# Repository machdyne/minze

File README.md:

# Minze Computer

Minze is an FPGA computer designed by Lone Dynamics Corporation.

This repo contains schematics, PCB layouts, pinouts, a 3D-printable case, example gateware and documentation.

Find more information on the [Minze product page](https://machdyne.com/product/minze-computer/).

## Programming Minze

Minze has a JTAG interface and ships with a [DFU bootloader](https://github.com/machdyne/tinydfu-bootloader) that allows the included flash [MMOD](https://machdyne.com/product/mmod) to be programmed over the USB-C port.

### DFU

The DFU bootloader is available for 5 seconds after power-on, issuing a DFU command during this period will stop the boot process until the DFU device is detached. If no command is received the boot process will continue and the user gateware will be loaded.

Install [dfu-util](http://dfu-util.sourceforge.net) (Debian/Ubuntu):

```
$ sudo apt install dfu-util
```

Update the user gateware on the flash MMOD:

```
$ sudo dfu-util -a 0 -D image.bit
```

Detach the DFU device and continue the boot process:

```
$ sudo dfu-util -a 0 -e
```

It is possible to update the bootloader itself using DFU but you shouldn't attempt this unless you have a JTAG programmer (or another method to program the MMOD) available, in case you need to restore the bootloader.

### JTAG

These examples assume you're using a "USB Blaster" JTAG cable, see the header pinout below. You will need to have [openFPGALoader](https://github.com/trabucayre/openFPGALoader) installed.

Program the configuration SRAM:

```
openFPGALoader -c usb-blaster image.bit
```

Program the flash MMOD:

```
openFPGALoader -f -c usb-blaster images/bootloader/tinydfu_minze.bit
```

## Blinky 

Building the blinky example requires [Yosys](https://github.com/YosysHQ/yosys), [nextpnr-ecp5](https://github.com/YosysHQ/nextpnr) and [Project Trellis](https://github.com/YosysHQ/prjtrellis).

Assuming they are installed, you can simply type `make` to build the gateware, which will be written to output/blinky.bin. You can then use [openFPGALoader](https://github.com/trabucayre/openFPGALoader) or dfu-util to write the gateware to the device.

## Linux

See the [Kakao Linux](https://github.com/machdyne/kakao) repo for the latest instructions.

### Prebuilt Images

Prebuilt gateware capable of running Linux is available in the `images/v1` directory.

These images support a serial console on the PMOD socket. You can use a standard USB-UART PMOD to access the BIOS, boot messages and serial console.

### Building Linux-capable Gateware

Please follow the setup instructions in the [linux-on-litex-vexriscv](https://github.com/litex-hub/linux-on-litex-vexriscv) repo and then:

1. Build the Linux-capable gateware:

```
$ cd linux-on-litex-vexriscv
$ ./make.py --board=minze --dcache-size=64 --icache-size=64 --uart-baudrate=115200 --build
$ ls build/minze
```

2. Write the gateware to the MMOD using USB DFU:

```
$ sudo dfu-util -a 0 -D build/minze/gateware/minze.bit
```

3. Copy the device tree binary `build/minze/minze.dtb` to a FAT-formatted MicroSD card.

## JTAG Header

The 3.3V JTAG header can be used to program the FPGA SRAM as well as the MMOD flash memory. It can also be used to provide power (5V) to the board.

```
6 5
4 3
2 1
```

| Pin | Signal |
| --- | ------ |
| 1 | TCK |
| 2 | TDI |
| 3 | TDO |
| 4 | TMS |
| 5 | 5V0 |
| 6 | GND |

## Board Revisions

| Revision | Notes |
| -------- | ----- |
| V1 | Initial production version |

## License

The contents of this repo are released under the [Lone Dynamics Open License](LICENSE.md) with the following exceptions:

- The KiCad design files contain parts of the [kicad-pmod](https://github.com/mithro/kicad-pmod) library which is released under the [Apache License, Version 2.0](https://www.apache.org/licenses/LICENSE-2.0.html).

- The KiCad design files may contain symbols and footprints released under other licenses; please contact us if we've failed to give proper attribution.

Note: You can use these designs for commercial purposes but we ask that instead of producing exact clones, that you either replace our trademarks and logos with your own or add your own next to ours.

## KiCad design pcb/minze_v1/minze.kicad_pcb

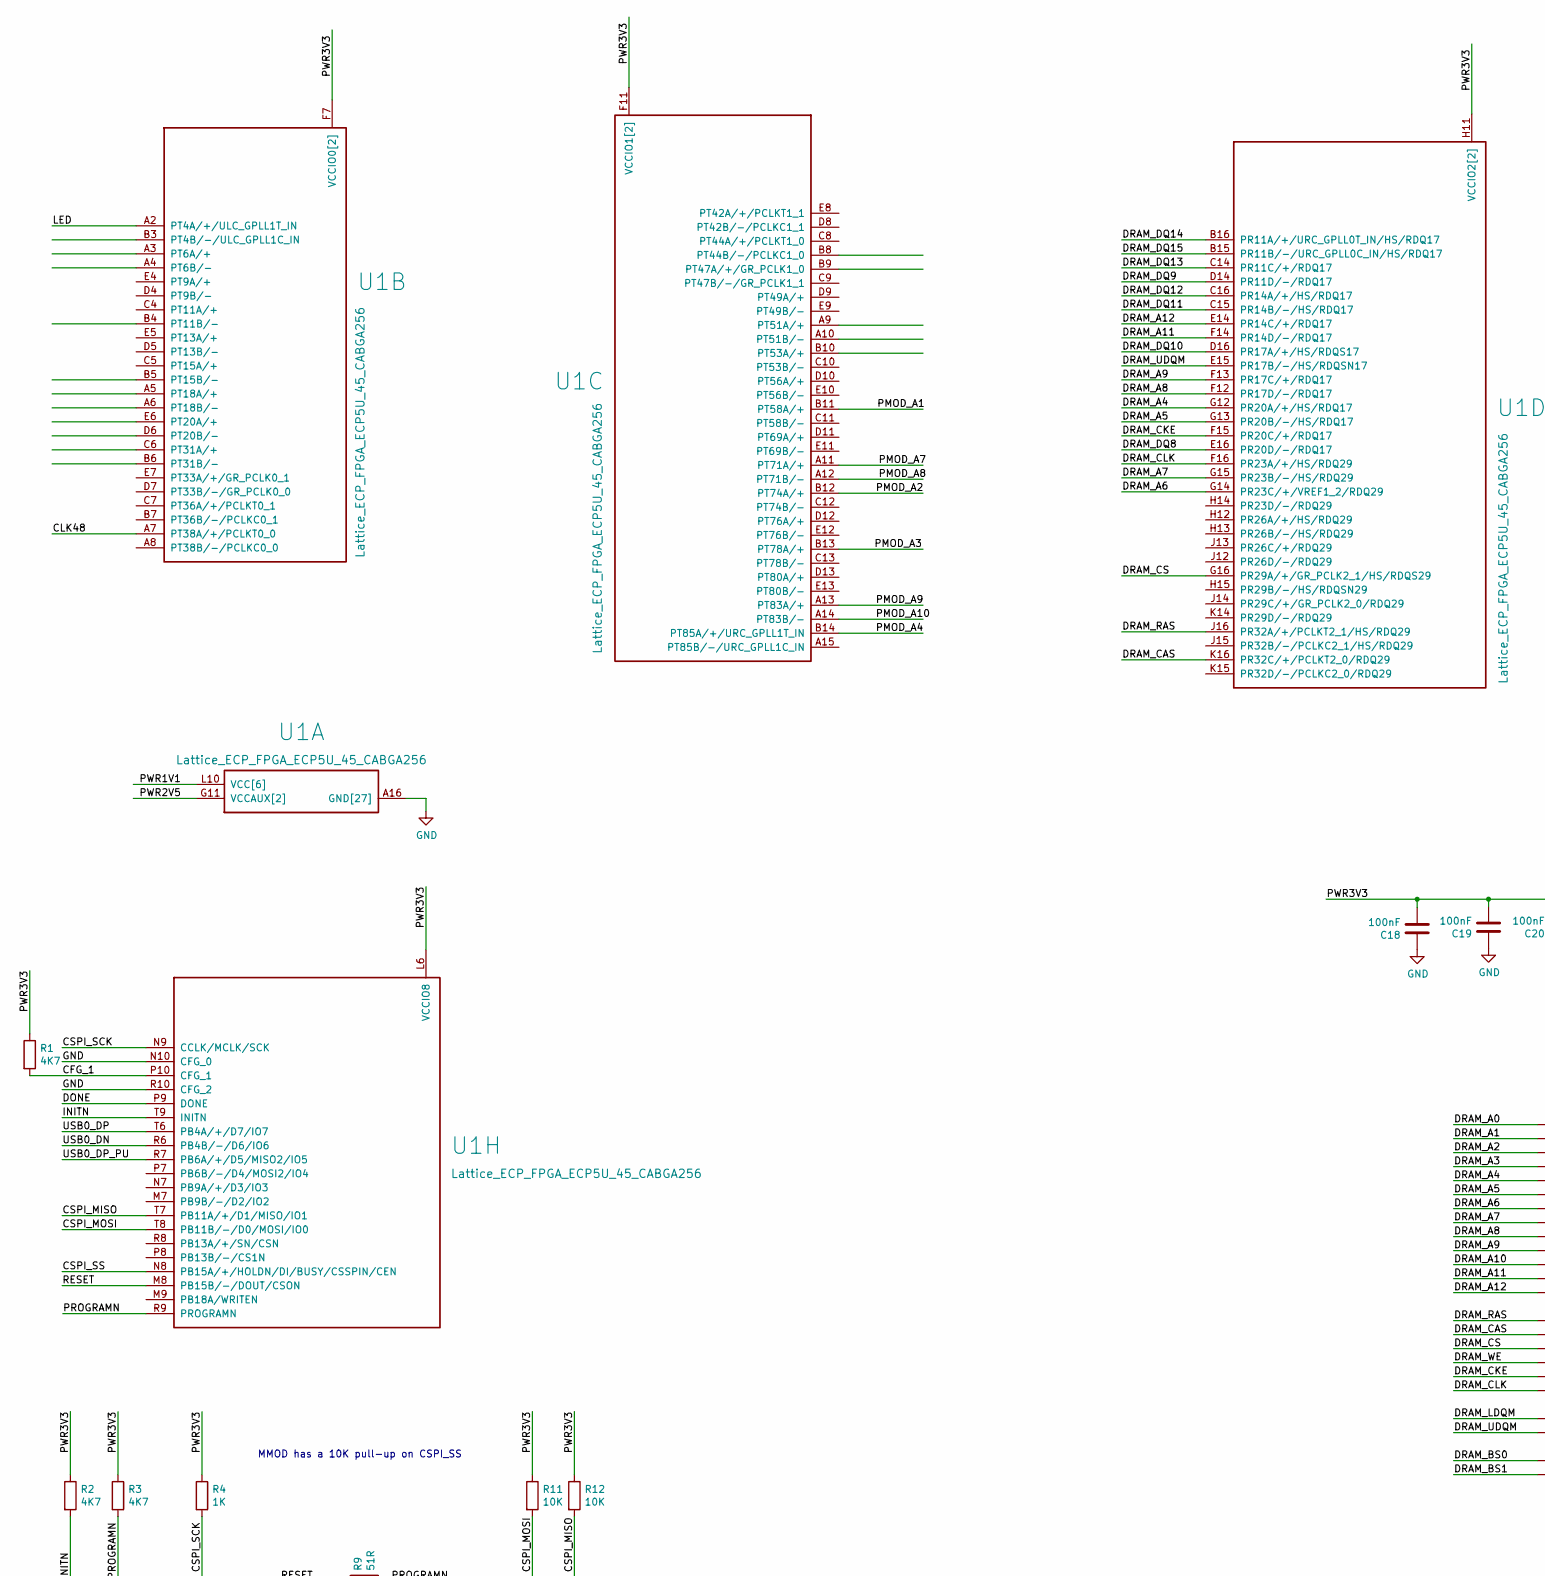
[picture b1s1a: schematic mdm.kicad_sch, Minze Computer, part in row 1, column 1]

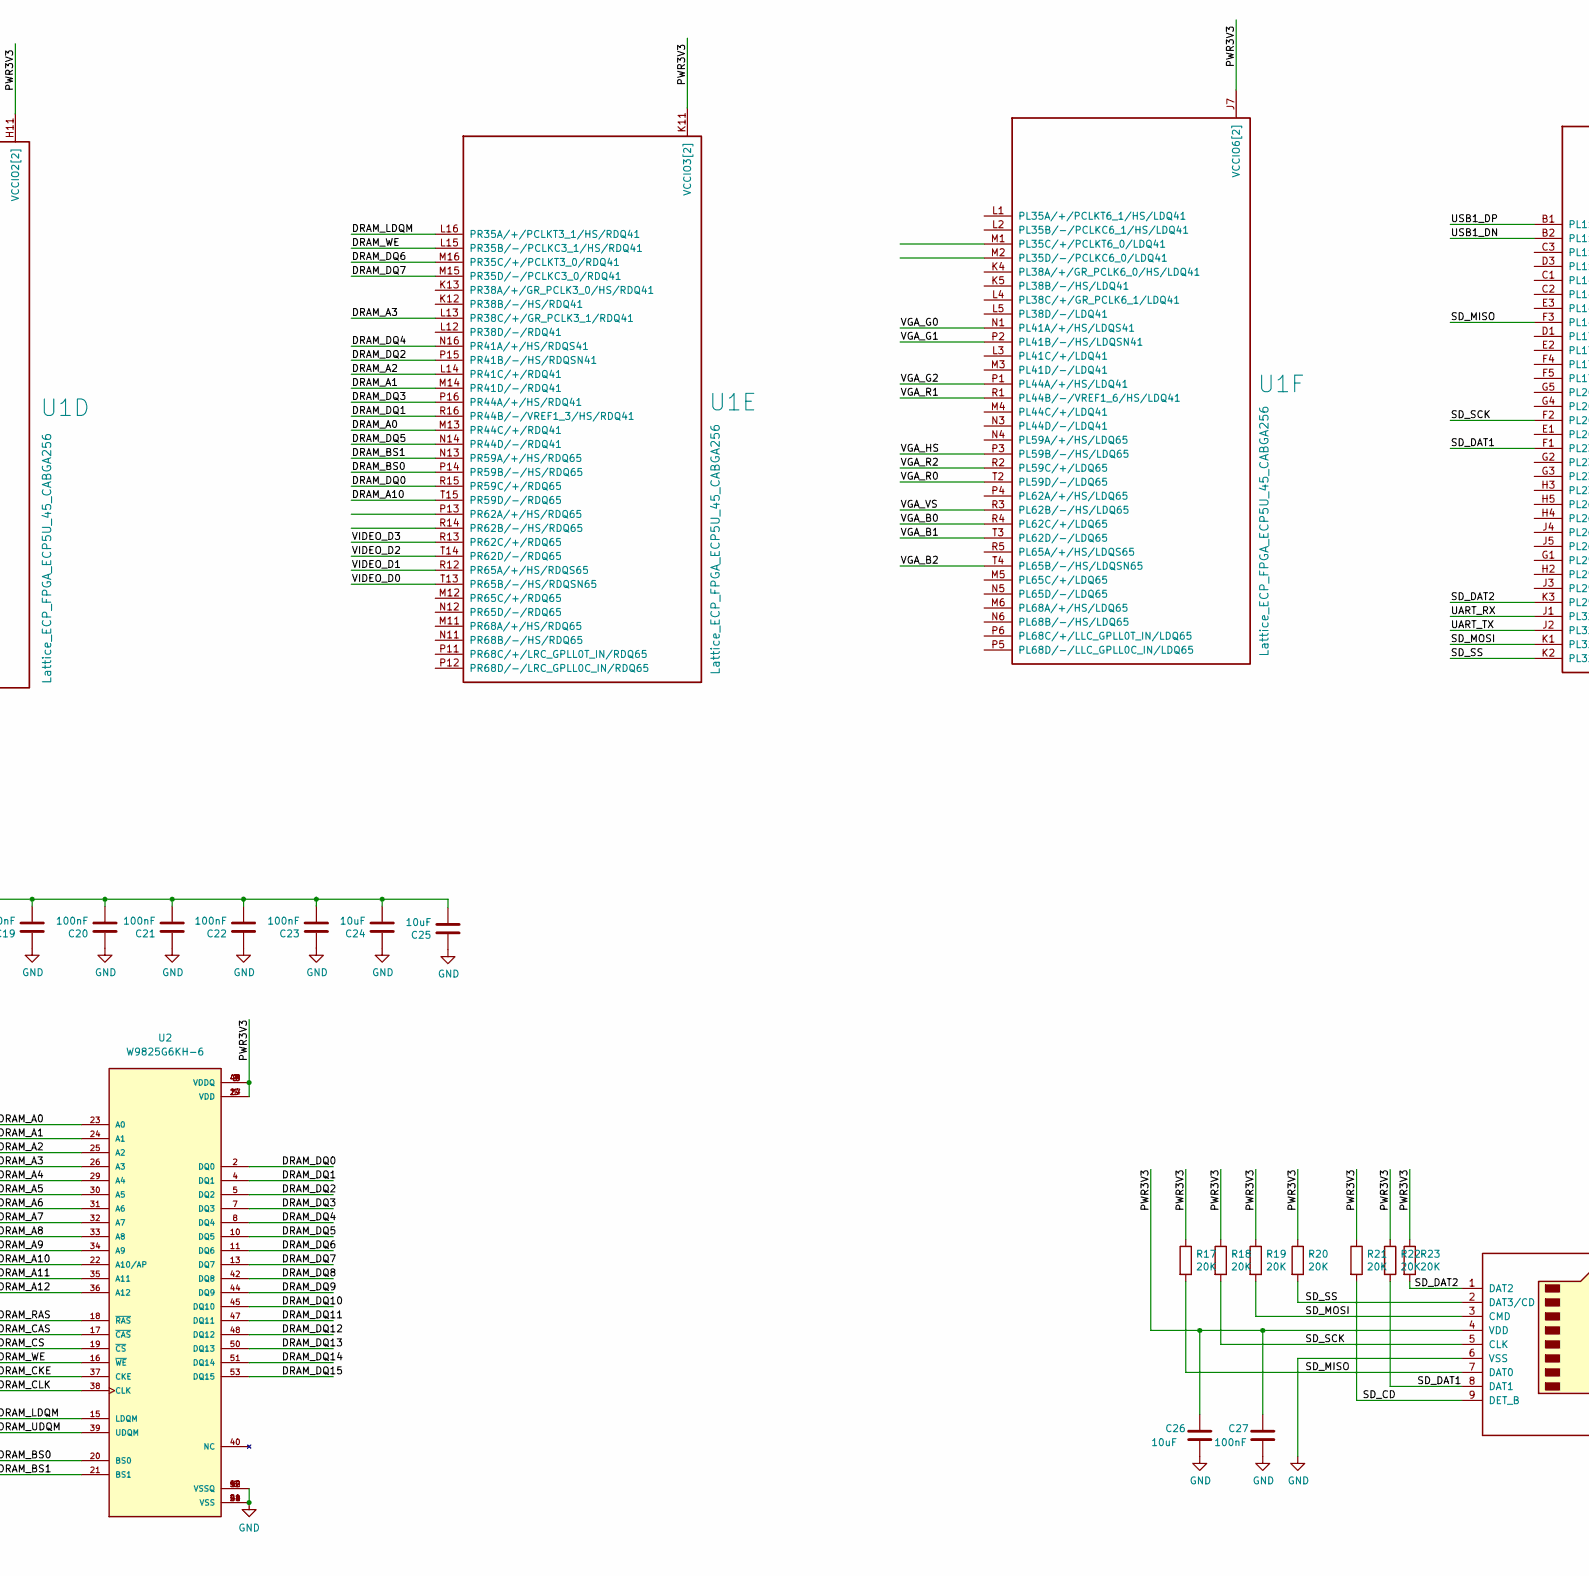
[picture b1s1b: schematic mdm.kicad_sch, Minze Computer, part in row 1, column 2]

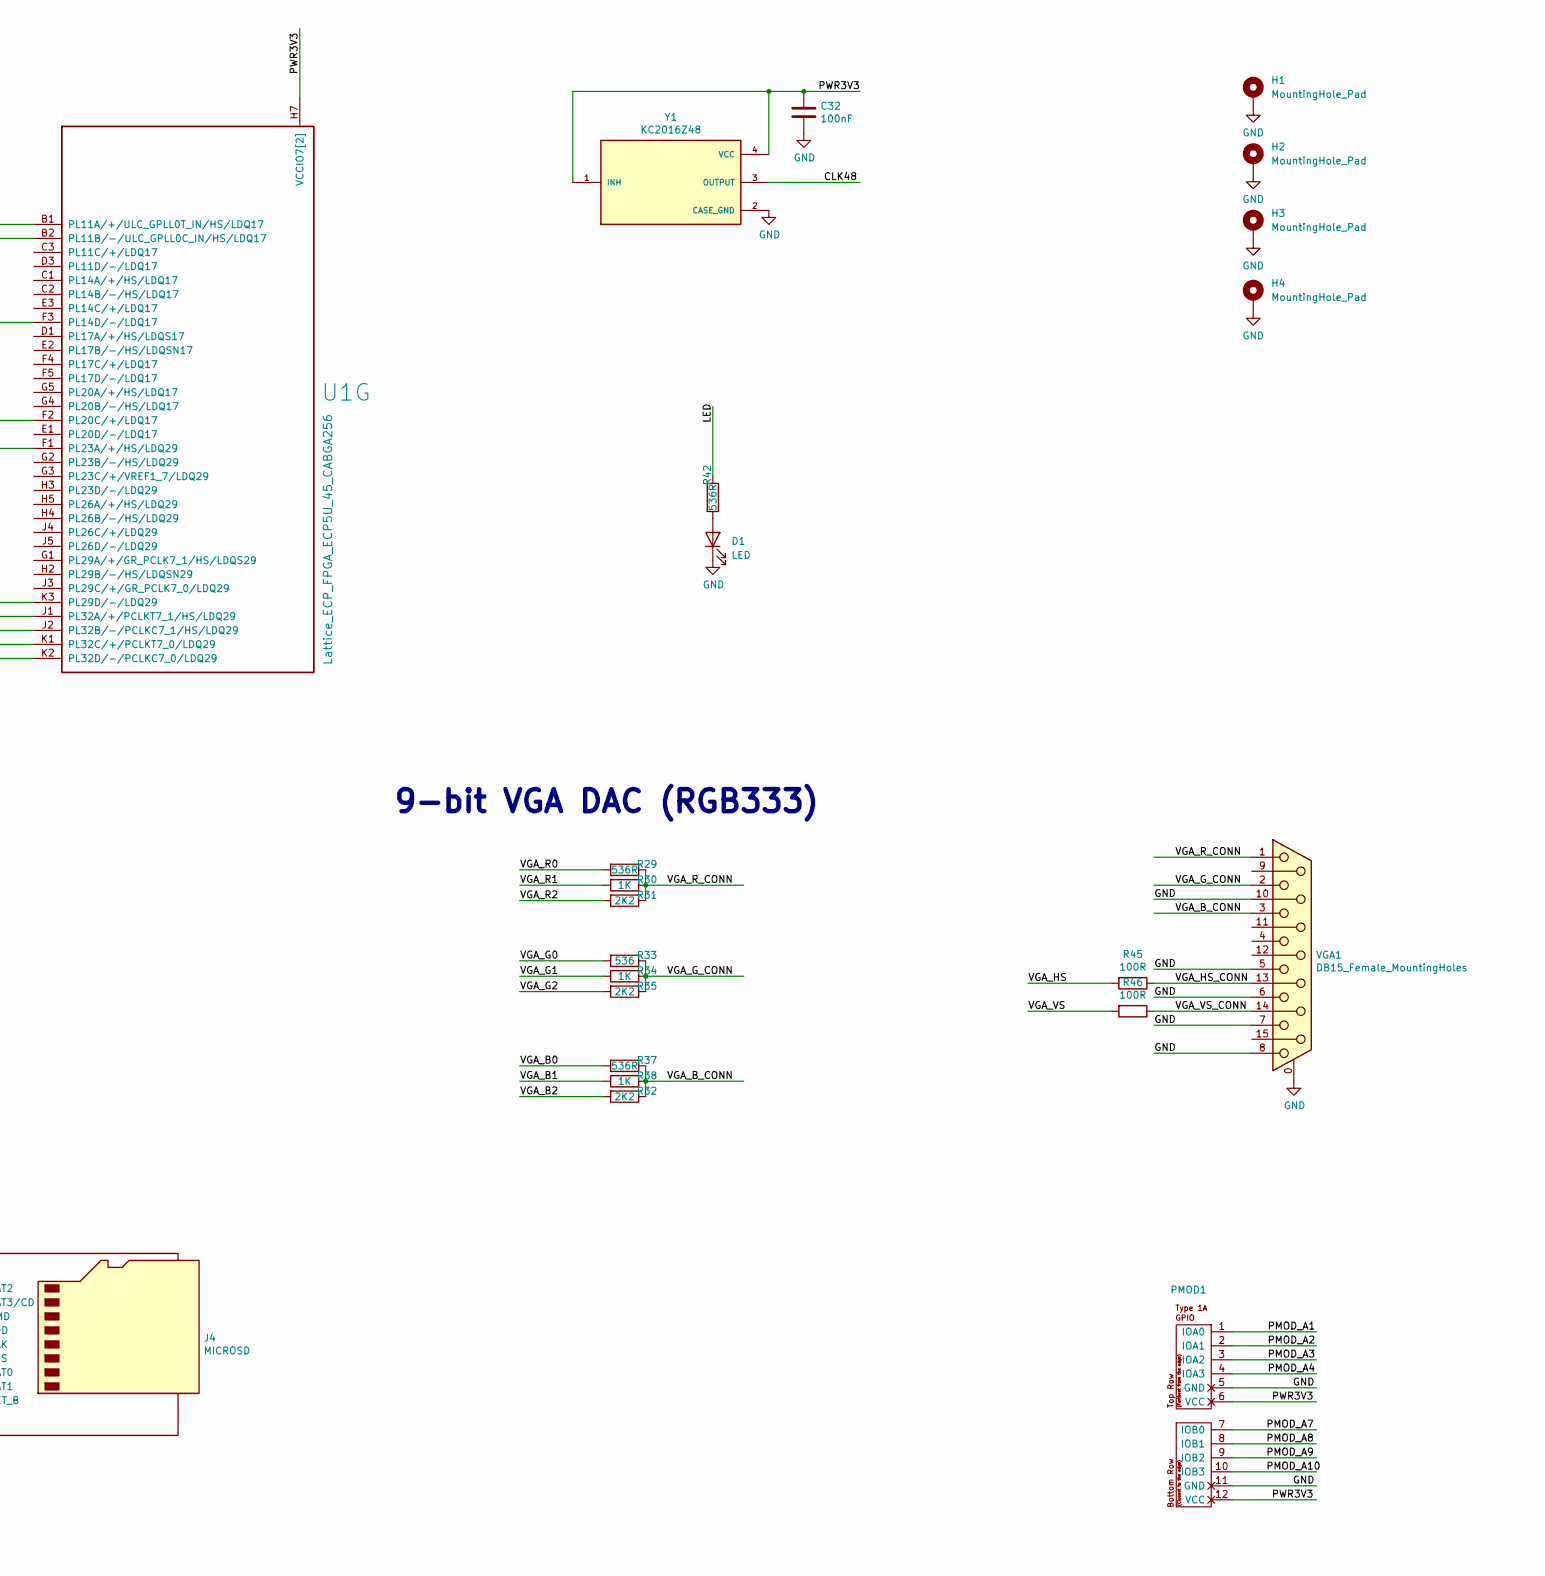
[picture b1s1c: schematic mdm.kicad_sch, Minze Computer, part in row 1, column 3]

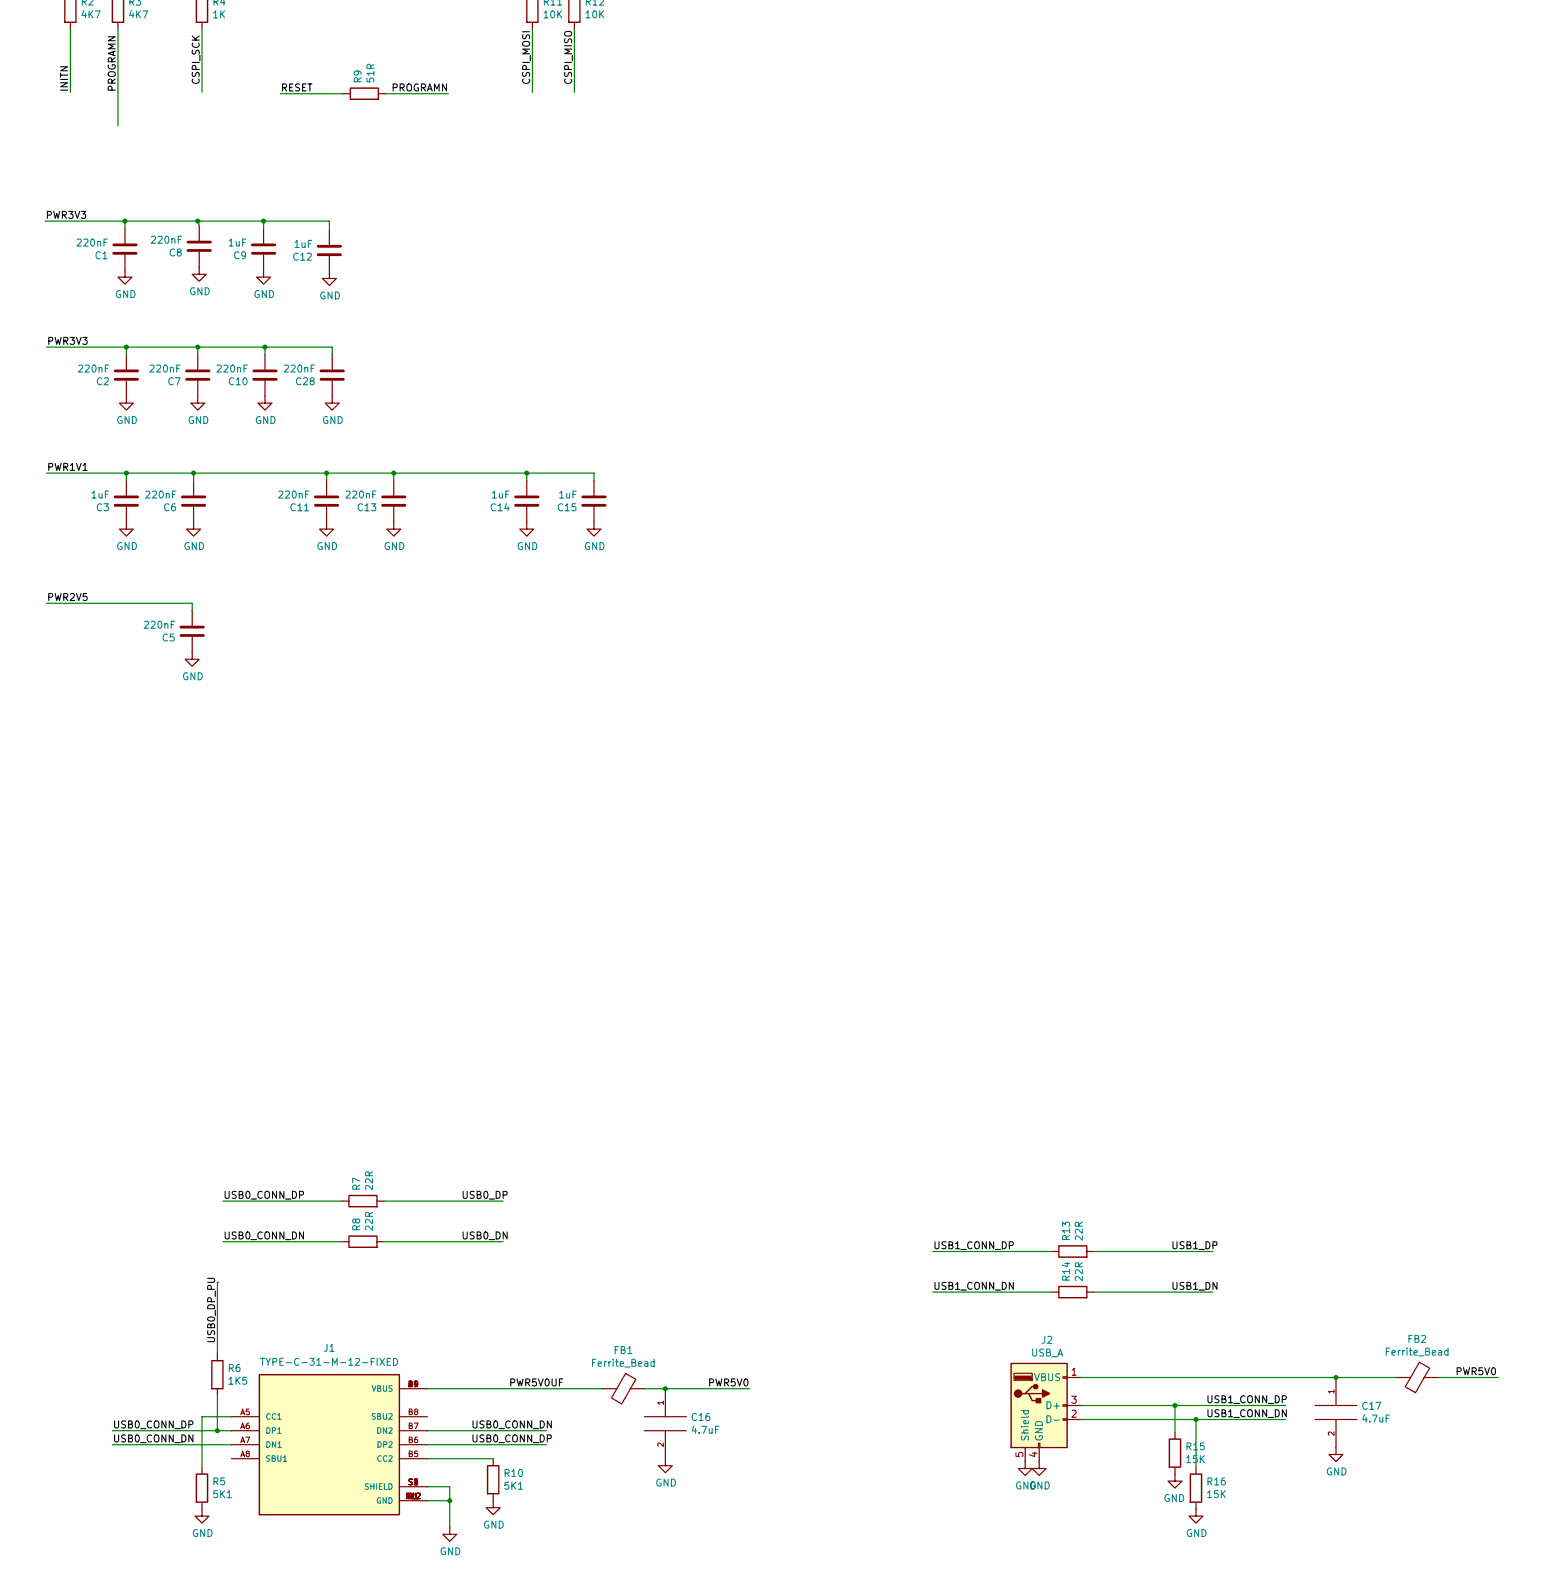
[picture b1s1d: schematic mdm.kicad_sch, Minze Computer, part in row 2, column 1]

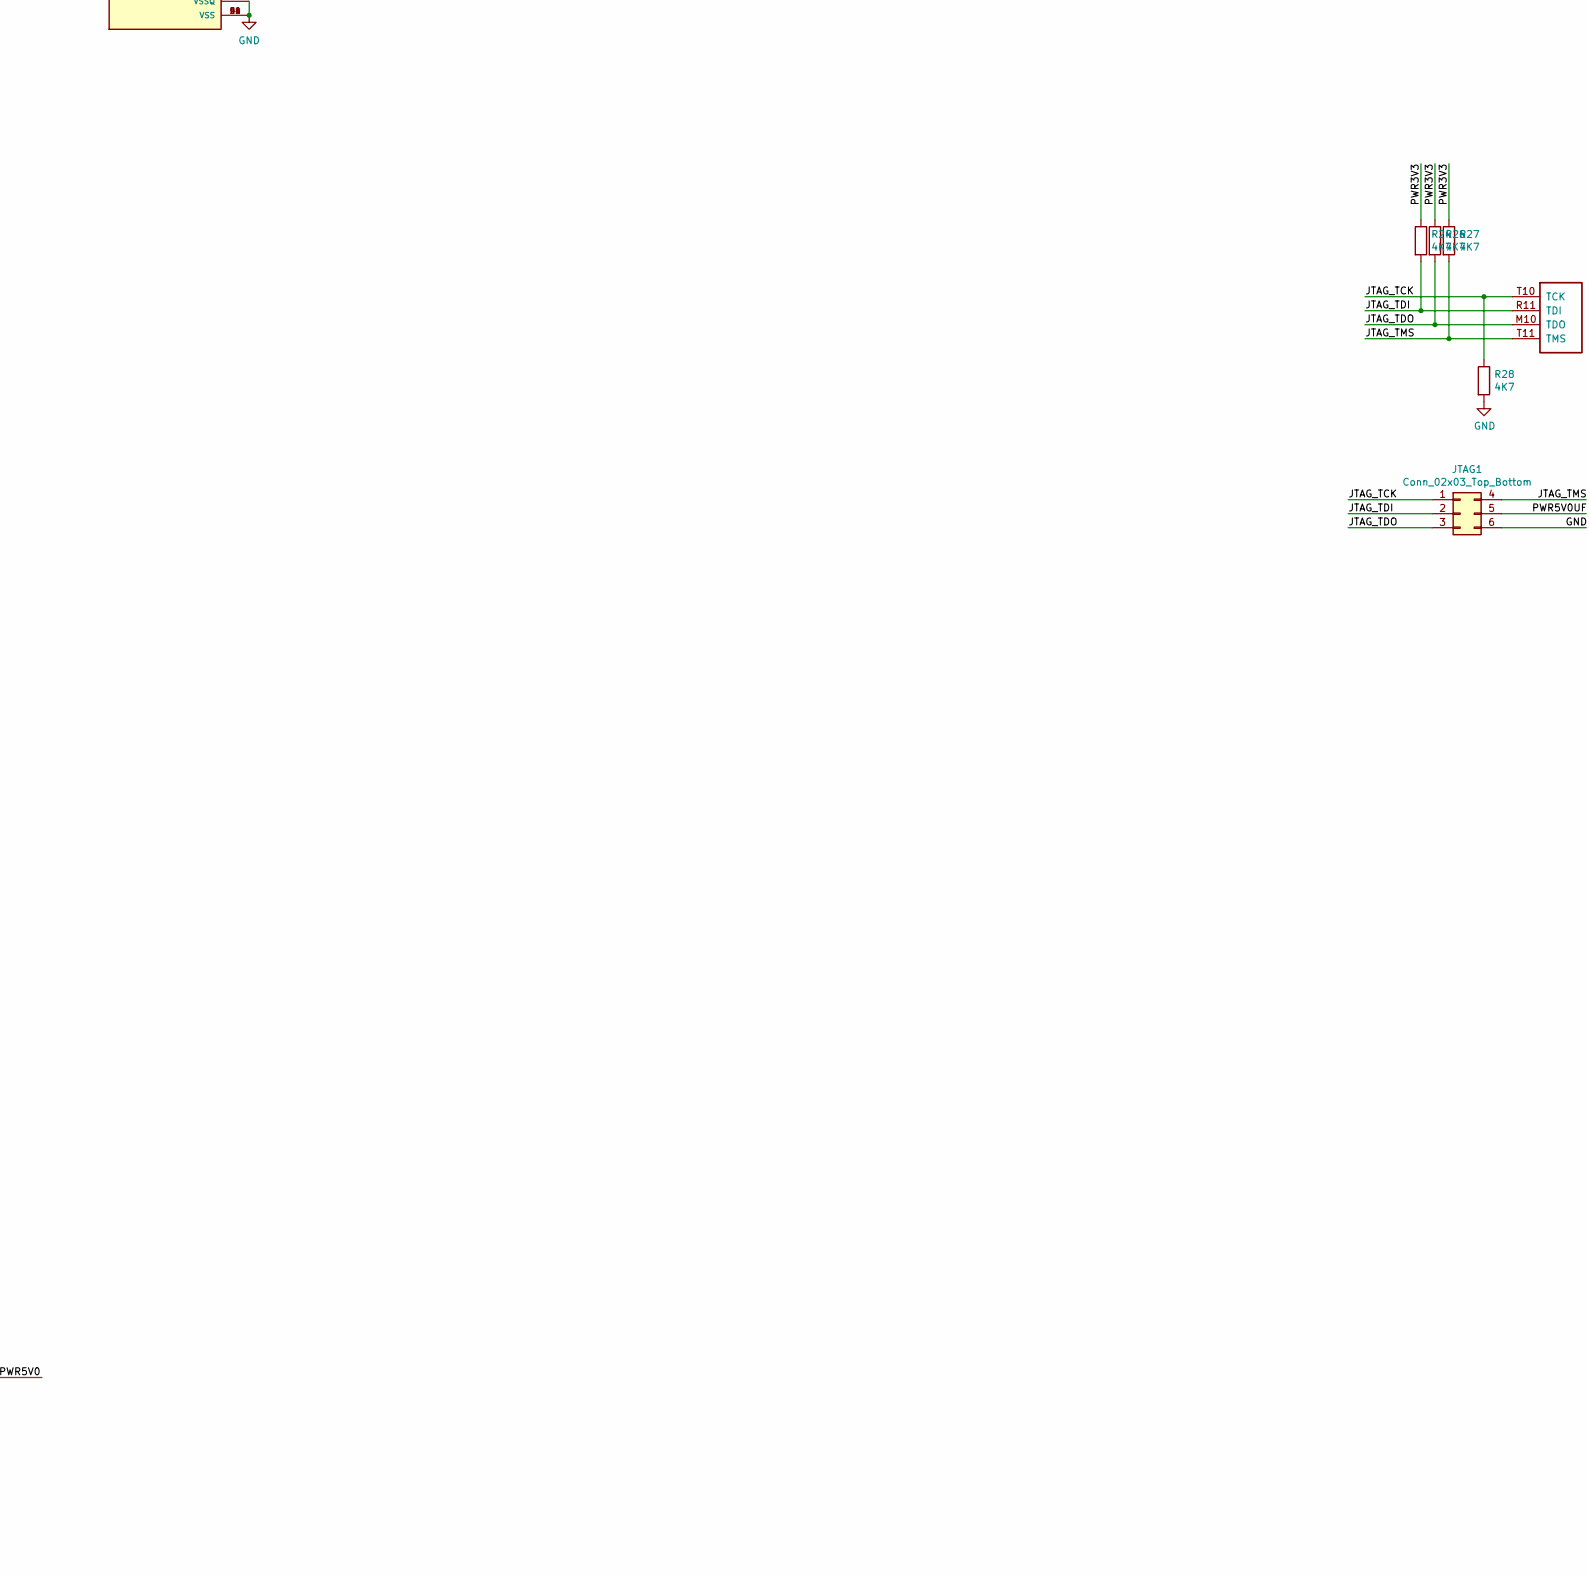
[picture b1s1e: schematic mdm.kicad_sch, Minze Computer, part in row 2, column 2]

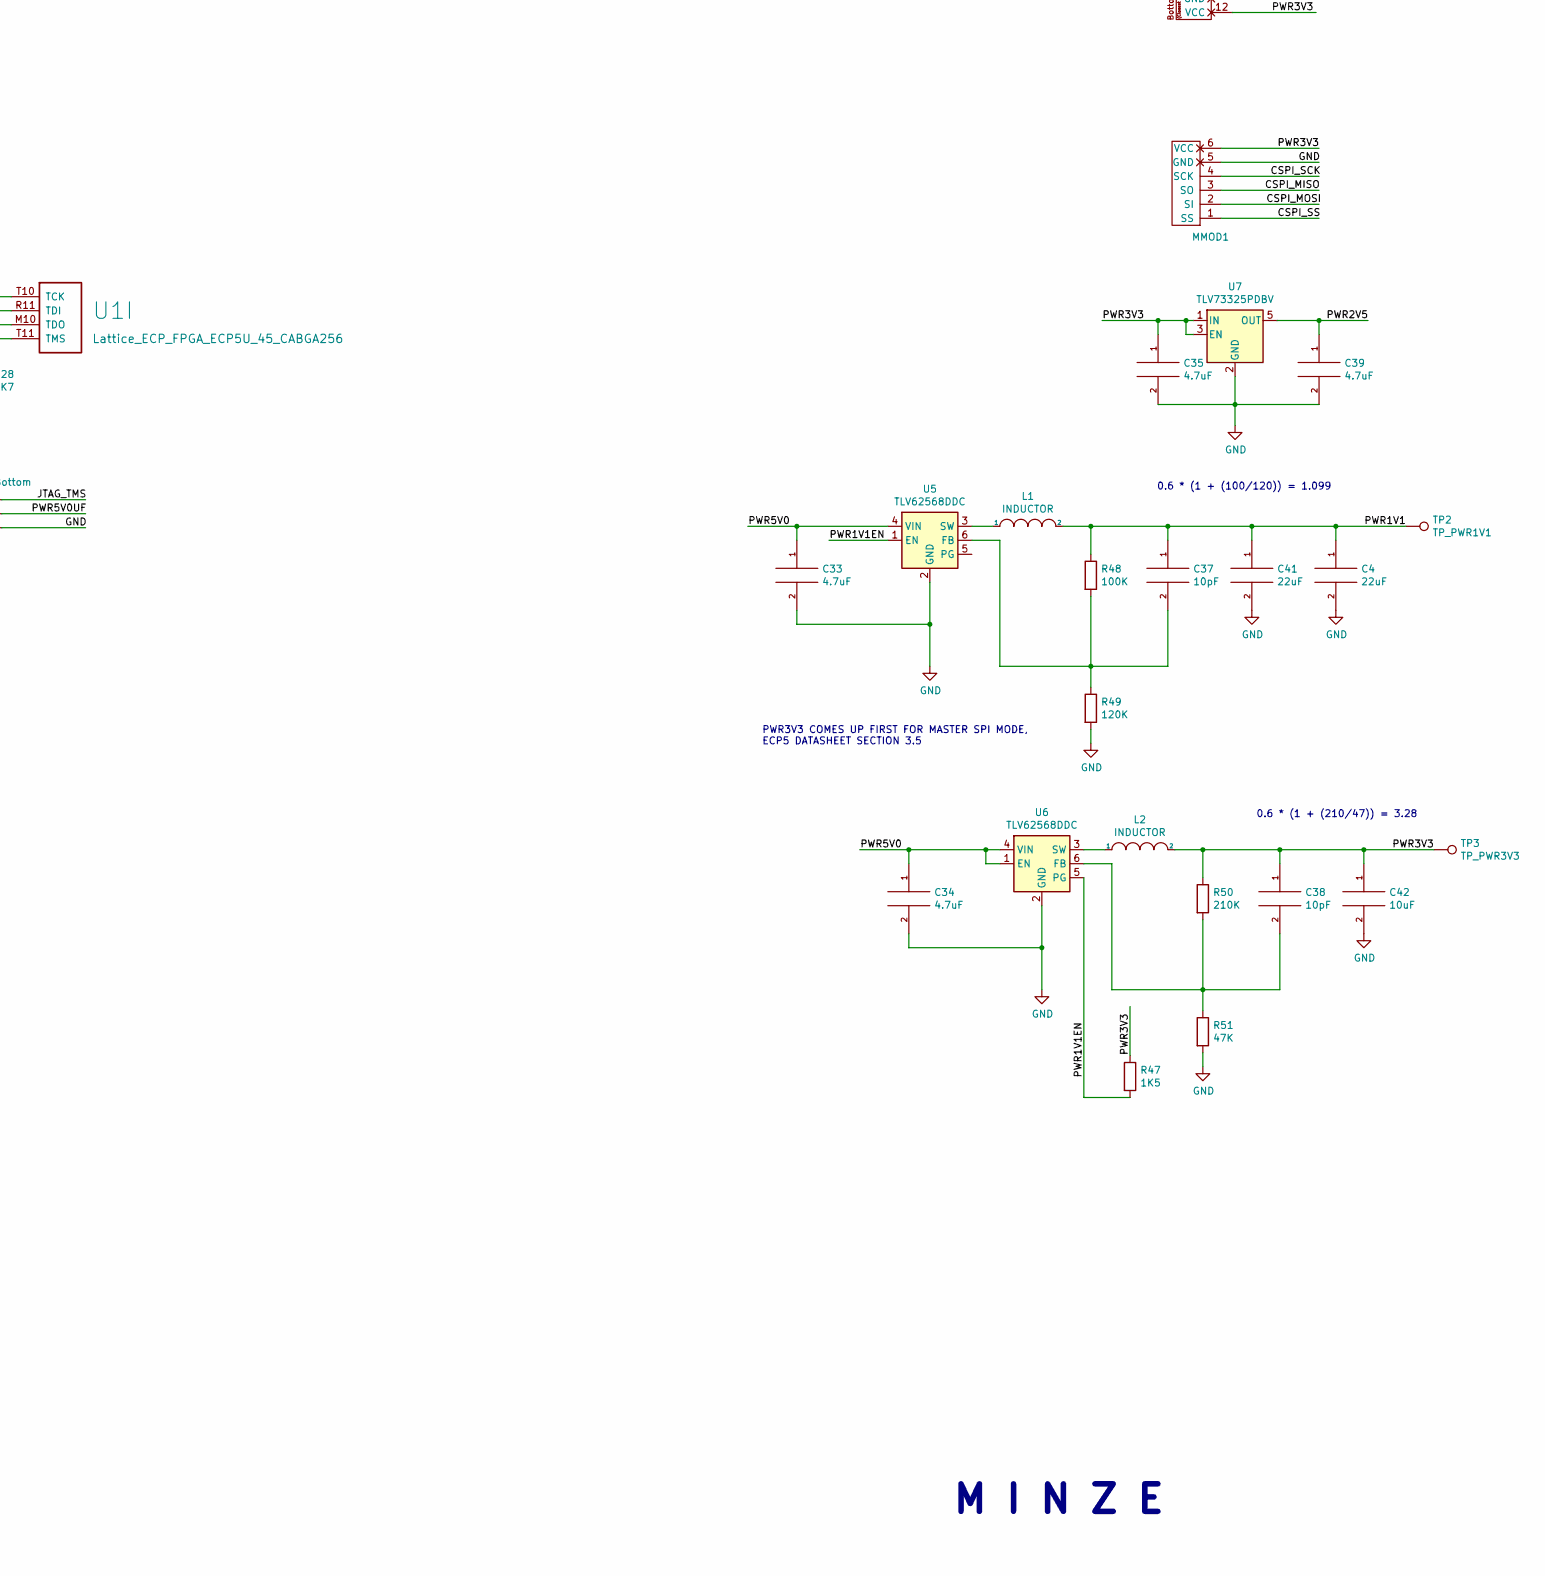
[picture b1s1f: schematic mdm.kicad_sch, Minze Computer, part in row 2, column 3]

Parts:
C1, C2, C5, C6, C7, C8, C10, C11, C13, C28: 220nF; C_0603_1608Metric
C3, C9, C12, C14, C15: 1uF; C_0603_1608Metric
C4, C41: 22uF; C_0603_1608Metric
C16, C17, C33, C34, C35, C39: 4.7uF; C_0603_1608Metric
C18, C19, C20, C21, C22, C23, C27, C32: 100nF; C_0603_1608Metric
C24, C25, C26, C42: 10uF; C_0603_1608Metric
C37, C38: 10pF; C_0603_1608Metric
D1: LED; LED_0603_1608Metric
FB1, FB2: Ferrite_Bead; R_0603_1608Metric
H1, H2, H3, H4: MountingHole_Pad; MountingHole_3.2mm_M3_Pad
J1: TYPE-C-31-M-12-FIXED; USB_C_Receptacle_HRO_TYPE-C-31-M-12-BIG-PADS; PARTREV A
J2: USB_A; USB_A_Stewart_SS-52100-001_Horizontal
J4: MICROSD; SDCARD
JTAG1: Conn_02x03_Top_Bottom; PinHeader_2x03_P2.54mm_Vertical
L1, L2: INDUCTOR; L_0805_2012Metric
MMOD1: PMOD-Device-x1-Type-2-SPI; MMOD_Host_Socket
PMOD1: PMOD-Device-x2-Type-1A-GPIO; PMOD_2x06_HOST
R1, R2, R3, R24, R26, R27, R28: 4K7; R_0603_1608Metric
R4, R30, R34, R38: 1K; R_0603_1608Metric
R5, R10: 5K1; R_0603_1608Metric
R6, R47: 1K5; R_0603_1608Metric
R7, R8, R13, R14: 22R; R_0603_1608Metric
R9: 51R; R_0603_1608Metric
R11, R12: 10K; R_0603_1608Metric
R15, R16: 15K; R_0603_1608Metric
R17, R18, R19, R20, R21, R22, R23: 20K; R_0603_1608Metric
R29, R37, R42: 536R; R_0603_1608Metric
R31, R32, R35: 2K2; R_0603_1608Metric
R33: 536; R_0603_1608Metric
R45, R46: 100R; R_0603_1608Metric
R48: 100K; R_0603_1608Metric
R49: 120K; R_0603_1608Metric
R50: 210K; R_0603_1608Metric
R51: 47K; R_0603_1608Metric
TP2: TP_PWR1V1; TestPoint_THTPad_D1.0mm_Drill0.5mm
TP3: TP_PWR3V3; TestPoint_THTPad_D1.0mm_Drill0.5mm
U1: Lattice_ECP_FPGA_ECP5U_45_CABGA256; BGA-256_14.0x14.0mm_Layout16x16_P0.8mm_Ball0.45mm_Pad0.32mm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
U2: W9825G6KH-6; SOP80P1176X120-54N; PARTREV A05
U5, U6: TLV62568DDC; SOT-23-6
U7: TLV73325PDBV; SOT-23-5
VGA1: DB15_Female_MountingHoles; DSUB-15-HD_Female_Horizontal_P2.29x1.98mm_EdgePinOffset3.03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
Y1: KC2016Z48; OSC_KC2016Z13.5600C1KX00; PARTREV November 2020

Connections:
/CFG_1: R1.2, U1.P10 (CFG_1)
/CLK48: U1.A7 (PT38A/+/PCLKT0_0), Y1.3 (OUTPUT)
/CSPI_MISO: MMOD1.3 (SO), R12.2, U1.T7 (PB11A/+/D1/MISO/IO1)
/CSPI_MOSI: MMOD1.2 (SI), R11.2, U1.T8 (PB11B/-/D0/MOSI/IO0)
/CSPI_SCK: MMOD1.4 (SCK), R4.2, U1.N9 (CCLK/MCLK/SCK)
/CSPI_SS: MMOD1.1 (SS), U1.N8 (PB15A/+/HOLDN/DI/BUSY/CSSPIN/CEN)
/DONE: U1.P9 (DONE)
/DRAM_A0: U1.M13 (PR44C/+/RDQ41), U2.23 (A0)
/DRAM_A1: U1.M14 (PR41D/-/RDQ41), U2.24 (A1)
/DRAM_A2: U1.L14 (PR41C/+/RDQ41), U2.25 (A2)
/DRAM_A3: U1.L13 (PR38C/+/GR_PCLK3_1/RDQ41), U2.26 (A3)
/DRAM_A4: U1.G12 (PR20A/+/HS/RDQ17), U2.29 (A4)
/DRAM_A5: U1.G13 (PR20B/-/HS/RDQ17), U2.30 (A5)
/DRAM_A6: U1.G14 (PR23C/+/VREF1_2/RDQ29), U2.31 (A6)
/DRAM_A7: U1.G15 (PR23B/-/HS/RDQ29), U2.32 (A7)
/DRAM_A8: U1.F12 (PR17D/-/RDQ17), U2.33 (A8)
/DRAM_A9: U1.F13 (PR17C/+/RDQ17), U2.34 (A9)
/DRAM_A10: U1.T15 (PR59D/-/RDQ65), U2.22 (A10/AP)
/DRAM_A11: U1.F14 (PR14D/-/RDQ17), U2.35 (A11)
/DRAM_A12: U1.E14 (PR14C/+/RDQ17), U2.36 (A12)
/DRAM_BS0: U1.P14 (PR59B/-/HS/RDQ65), U2.20 (BS0)
/DRAM_BS1: U1.N13 (PR59A/+/HS/RDQ65), U2.21 (BS1)
/DRAM_CAS: U1.K16 (PR32C/+/PCLKT2_0/RDQ29), U2.17 (~CAS)
/DRAM_CKE: U1.F15 (PR20C/+/RDQ17), U2.37 (CKE)
/DRAM_CLK: U1.F16 (PR23A/+/HS/RDQ29), U2.38 (CLK)
/DRAM_CS: U1.G16 (PR29A/+/GR_PCLK2_1/HS/RDQS29), U2.19 (~CS)
/DRAM_DQ0: U1.R15 (PR59C/+/RDQ65), U2.2 (DQ0)
/DRAM_DQ1: U1.R16 (PR44B/-/VREF1_3/HS/RDQ41), U2.4 (DQ1)
/DRAM_DQ2: U1.P15 (PR41B/-/HS/RDQSN41), U2.5 (DQ2)
/DRAM_DQ3: U1.P16 (PR44A/+/HS/RDQ41), U2.7 (DQ3)
/DRAM_DQ4: U1.N16 (PR41A/+/HS/RDQS41), U2.8 (DQ4)
/DRAM_DQ5: U1.N14 (PR44D/-/RDQ41), U2.10 (DQ5)
/DRAM_DQ6: U1.M16 (PR35C/+/PCLKT3_0/RDQ41), U2.11 (DQ6)
/DRAM_DQ7: U1.M15 (PR35D/-/PCLKC3_0/RDQ41), U2.13 (DQ7)
/DRAM_DQ8: U1.E16 (PR20D/-/RDQ17), U2.42 (DQ8)
/DRAM_DQ9: U1.D14 (PR11D/-/RDQ17), U2.44 (DQ9)
/DRAM_DQ10: U1.D16 (PR17A/+/HS/RDQS17), U2.45 (DQ10)
/DRAM_DQ11: U1.C15 (PR14B/-/HS/RDQ17), U2.47 (DQ11)
/DRAM_DQ12: U1.C16 (PR14A/+/HS/RDQ17), U2.48 (DQ12)
/DRAM_DQ13: U1.C14 (PR11C/+/RDQ17), U2.50 (DQ13)
/DRAM_DQ14: U1.B16 (PR11A/+/URC_GPLL0T_IN/HS/RDQ17), U2.51 (DQ14)
/DRAM_DQ15: U1.B15 (PR11B/-/URC_GPLL0C_IN/HS/RDQ17), U2.53 (DQ15)
/DRAM_LDQM: U1.L16 (PR35A/+/PCLKT3_1/HS/RDQ41), U2.15 (LDQM)
/DRAM_RAS: U1.J16 (PR32A/+/PCLKT2_1/HS/RDQ29), U2.18 (~RAS)
/DRAM_UDQM: U1.E15 (PR17B/-/HS/RDQSN17), U2.39 (UDQM)
/DRAM_WE: U1.L15 (PR35B/-/PCLKC3_1/HS/RDQ41), U2.16 (~WE)
/INITN: R2.2, U1.T9 (INITN)
/JTAG_TCK: JTAG1.1, R28.1, U1.T10 (TCK)
/JTAG_TDI: JTAG1.2, R24.2, U1.R11 (TDI)
/JTAG_TDO: JTAG1.3, R26.2, U1.M10 (TDO)
/JTAG_TMS: JTAG1.4, R27.2, U1.T11 (TMS)
/LED: R42.1, U1.A2 (PT4A/+/ULC_GPLL1T_IN)
/PMOD_A1: PMOD1.1 (IOA0), U1.B11 (PT58A/+)
/PMOD_A2: PMOD1.2 (IOA1), U1.B12 (PT74A/+)
/PMOD_A3: PMOD1.3 (IOA2), U1.B13 (PT78A/+)
/PMOD_A4: PMOD1.4 (IOA3), U1.B14 (PT85A/+/URC_GPLL1T_IN)
/PMOD_A7: PMOD1.7 (IOB0), U1.A11 (PT71A/+)
/PMOD_A8: PMOD1.8 (IOB1), U1.A12 (PT71B/-)
/PMOD_A9: PMOD1.9 (IOB2), U1.A13 (PT83A/+)
/PMOD_A10: PMOD1.10 (IOB3), U1.A14 (PT83B/-)
/PROGRAMN: R3.2, R9.2, U1.R9 (PROGRAMN)
/PWR1V1: C3.2, C4.1, C6.2, C11.2, C13.2, C14.2, C15.2, C37.1, C41.1, L1.2, R48.1, TP2.1, U1.G6 (VCC[6]), U1.G7 (VCC[6]), U1.G9 (VCC[6]), U1.L8 (VCC[6]), U1.L9 (VCC[6]), U1.L10 (VCC[6])
/PWR1V1EN: R47.2, U5.1 (EN), U6.5 (PG)
/PWR2V5: C5.2, C39.1, U1.G11 (VCCAUX[2]), U1.L7 (VCCAUX[2]), U7.5 (OUT)
/PWR3V3: C1.2, C2.2, C7.2, C8.2, C9.2, C10.2, C12.2, C18.2, C19.2, C20.2, C21.2, C22.2, C23.2, C24.2, C25.2, C26.1, C27.1, C28.2, C32.1, C35.1, C38.1, C42.1, J4.4 (VDD), L2.2, MMOD1.6 (VCC), PMOD1.6 (VCC), PMOD1.12 (VCC), R1.1, R2.1, R3.1, R4.1, R11.1, R12.1, R17.1, R18.1, R19.1, R20.1, R21.1, R22.1, R23.1, R24.1, R26.1, R27.1, R47.1, R50.1, TP3.1, U1.F6 (VCCIO0[2]), U1.F7 (VCCIO0[2]), U1.F10 (VCCIO1[2]), U1.F11 (VCCIO1[2]), U1.H6 (VCCIO7[2]), U1.H7 (VCCIO7[2]), U1.H11 (VCCIO2[2]), U1.J6 (VCCIO6[2]), U1.J7 (VCCIO6[2]), U1.J11 (VCCIO2[2]), U1.K11 (VCCIO3[2]), U1.L6 (VCCIO8), U1.L11 (VCCIO3[2]), U2.1 (VDD), U2.3 (VDDQ), U2.9 (VDDQ), U2.14 (VDD), U2.27 (VDD), U2.43 (VDDQ), U2.49 (VDDQ), U7.1 (IN), U7.3 (EN), Y1.1 (INH), Y1.4 (VCC)
/PWR5V0: C16.1, C33.1, C34.1, FB1.1, FB2.1, U5.4 (VIN), U6.1 (EN), U6.4 (VIN)
/PWR5V0UF: FB1.2, J1.A4 (VBUS), J1.A9 (VBUS), J1.B4 (VBUS), J1.B9 (VBUS), JTAG1.5
/RESET: R9.1, U1.M8 (PB15B/-/DOUT/CSON)
/SD_CD: J4.9 (DET_B), R21.2
/SD_DAT1: J4.8 (DAT1), R22.2, U1.F1 (PL23A/+/HS/LDQ29)
/SD_DAT2: J4.1 (DAT2), R23.2, U1.K3 (PL29D/-/LDQ29)
/SD_MISO: J4.7 (DAT0), R17.2, U1.F3 (PL14D/-/LDQ17)
/SD_MOSI: J4.3 (CMD), R19.2, U1.K1 (PL32C/+/PCLKT7_0/LDQ29)
/SD_SCK: J4.5 (CLK), R18.2, U1.F2 (PL20C/+/LDQ17)
/SD_SS: J4.2 (DAT3/CD), R20.2, U1.K2 (PL32D/-/PCLKC7_0/LDQ29)
/UART_RX: U1.J1 (PL32A/+/PCLKT7_1/HS/LDQ29)
/UART_TX: U1.J2 (PL32B/-/PCLKC7_1/HS/LDQ29)
/USB0_CONN_DN: J1.A7 (DN1), J1.B7 (DN2), R8.1
/USB0_CONN_DP: J1.A6 (DP1), J1.B6 (DP2), R6.2, R7.1
/USB0_DN: R8.2, U1.R6 (PB4B/-/D6/IO6)
/USB0_DP: R7.2, U1.T6 (PB4A/+/D7/IO7)
/USB0_DP_PU: R6.1, U1.R7 (PB6A/+/D5/MISO2/IO5)
/USB1_CONN_DN: J2.2 (D-), R14.1, R16.1
/USB1_CONN_DP: J2.3 (D+), R13.1, R15.1
/USB1_DN: R14.2, U1.B2 (PL11B/-/ULC_GPLL0C_IN/HS/LDQ17)
/USB1_DP: R13.2, U1.B1 (PL11A/+/ULC_GPLL0T_IN/HS/LDQ17)
/VGA_B0: R37.2, U1.R4 (PL62C/+/LDQ65)
/VGA_B1: R38.2, U1.T3 (PL62D/-/LDQ65)
/VGA_B2: R32.2, U1.T4 (PL65B/-/HS/LDQSN65)
/VGA_B_CONN: R32.1, R37.1, R38.1, VGA1.3
/VGA_G0: R33.2, U1.N1 (PL41A/+/HS/LDQS41)
/VGA_G1: R34.2, U1.P2 (PL41B/-/HS/LDQSN41)
/VGA_G2: R35.2, U1.P1 (PL44A/+/HS/LDQ41)
/VGA_G_CONN: R33.1, R34.1, R35.1, VGA1.2
/VGA_HS: R45.2, U1.P3 (PL59B/-/HS/LDQ65)
/VGA_HS_CONN: R45.1, VGA1.13
/VGA_R0: R29.2, U1.T2 (PL59D/-/LDQ65)
/VGA_R1: R30.2, U1.R1 (PL44B/-/VREF1_6/HS/LDQ41)
/VGA_R2: R31.2, U1.R2 (PL59C/+/LDQ65)
/VGA_R_CONN: R29.1, R30.1, R31.1, VGA1.1
/VGA_VS: R46.2, U1.R3 (PL62B/-/HS/LDQ65)
/VGA_VS_CONN: R46.1, VGA1.14
/VIDEO_D0: U1.T13 (PR65B/-/HS/RDQSN65)
/VIDEO_D1: U1.R12 (PR65A/+/HS/RDQS65)
/VIDEO_D2: U1.T14 (PR62D/-/RDQ65)
/VIDEO_D3: U1.R13 (PR62C/+/RDQ65)
GND: C1.1, C2.1, C3.1, C4.2, C5.1, C6.1, C7.1, C8.1, C9.1, C10.1, C11.1, C12.1, C13.1, C14.1, C15.1, C16.2, C17.2, C18.1, C19.1, C20.1, C21.1, C22.1, C23.1, C24.1, C25.1, C26.2, C27.2, C28.1, C32.2, C33.2, C34.2, C35.2, C39.2, C41.2, C42.2, D1.1 (K), H1.1, H2.1, H3.1, H4.1, J1.A1 (GND), J1.A12 (GND), J1.B1 (GND), J1.B12 (GND), J1.S1 (SHIELD), J1.S2 (SHIELD), J1.S3 (SHIELD), J1.S4 (SHIELD), J2.4 (GND), J2.5 (Shield), J4.6 (VSS), JTAG1.6, MMOD1.5 (GND), PMOD1.5 (GND), PMOD1.11 (GND), R5.2, R10.2, R15.2, R16.2, R28.2, R49.2, R51.2, U1.A1 (GND[27]), U1.A16 (GND[27]), U1.D2 (GND[27]), U1.D15 (GND[27]), U1.F8 (GND[27]), U1.F9 (GND[27]), U1.G8 (GND[27]), U1.G10 (GND[27]), U1.H1 (GND[27]), U1.H8 (GND[27]), U1.H9 (GND[27]), U1.H10 (GND[27]), U1.H16 (GND[27]), U1.J8 (GND[27]), U1.J9 (GND[27]), U1.J10 (GND[27]), U1.K6 (GND[27]), U1.K7 (GND[27]), U1.K8 (GND[27]), U1.K9 (GND[27]), U1.K10 (GND[27]), U1.N2 (GND[27]), U1.N10 (CFG_0), U1.N15 (GND[27]), U1.R10 (CFG_2), U1.T1 (GND[27]), U1.T5 (GND[27]), U1.T12 (GND[27]), U1.T16 (GND[27]), U2.6 (VSSQ), U2.12 (VSSQ), U2.28 (VSS), U2.41 (VSS), U2.46 (VSSQ), U2.52 (VSSQ), U2.54 (VSS), U5.2 (GND), U6.2 (GND), U7.2 (GND), VGA1.0 (PAD), VGA1.5, VGA1.6, VGA1.7, VGA1.8, VGA1.10, Y1.2 (CASE_GND)
unnamed: C17.1, FB2.2, J2.1 (VBUS)
unnamed: C37.2, R48.2, R49.1, U5.6 (FB)
unnamed: C38.2, R50.2, R51.1, U6.6 (FB)
unnamed: D1.2 (A), R42.2
unnamed: J1.A5 (CC1), R5.1
unnamed: J1.B5 (CC2), R10.1
unnamed: L1.1, U5.3 (SW)
unnamed: L2.1, U6.3 (SW)

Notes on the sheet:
M I N Z E
PWR3V3 COMES UP FIRST FOR MASTER SPI MODE, ECP5 DATASHEET SECTION 3.5
0.6 * (1 + (210/47)) = 3.28
MMOD has a 10K pull-up on CSPI_SS
0.6 * (1 + (100/120)) = 1.099
9-bit VGA DAC (RGB333)

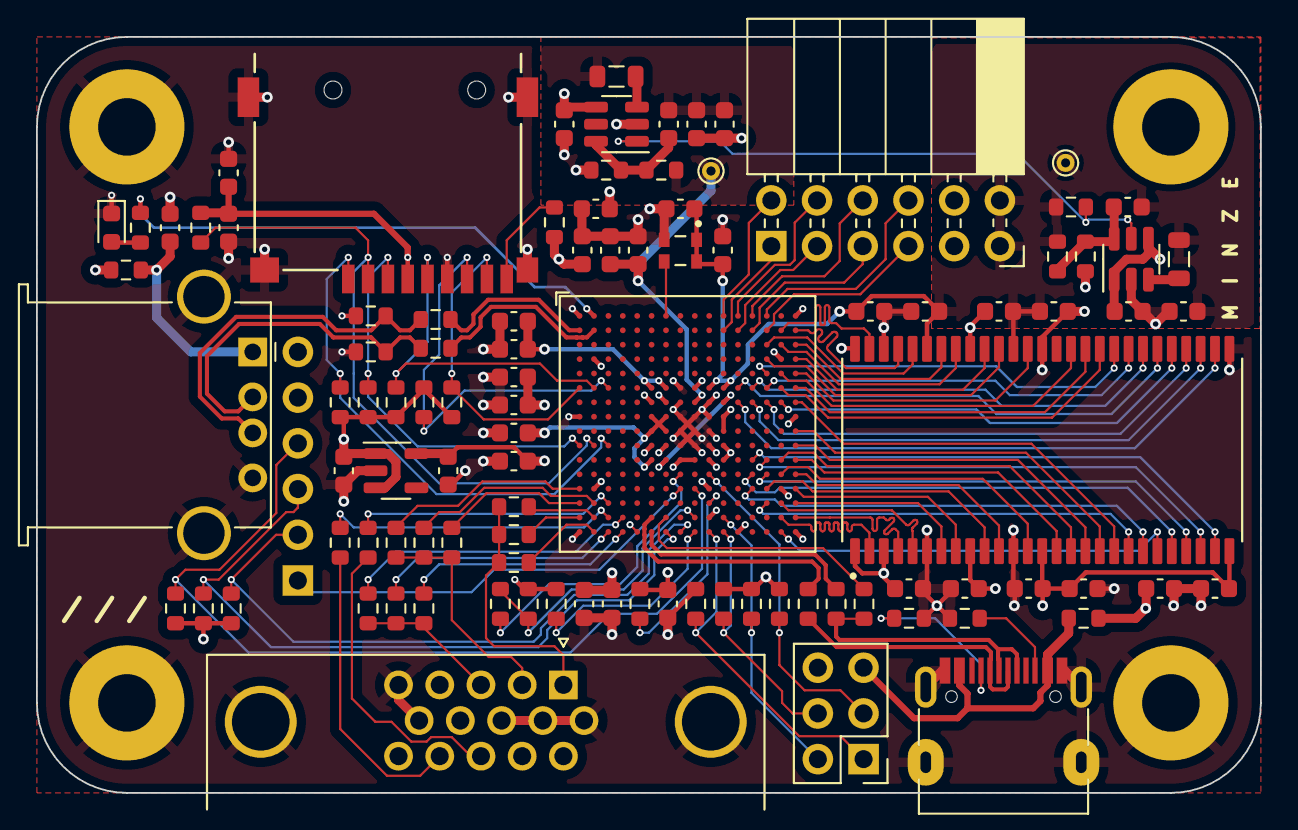
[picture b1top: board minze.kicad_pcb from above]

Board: 4 copper layers, 68.0 x 42.0 mm, 105 parts (1 on the bottom side), 108 nets.

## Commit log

2023-12-11 add image
2023-12-11 rename kicad files
2023-12-11 add images
2023-12-27 add dfu bootloader
2023-12-28 add case
2023-12-31 minor structural improvements
2024-05-29 update bitstream
2024-05-29 increase bottom height
2024-09-10 fix boot.json
2024-09-10 add monochrome bitstreams
2024-09-12 add sdroot dtb
2024-09-23 fix jtag diagram

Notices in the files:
pcb/minze_v1/mdm.kicad_sch:
Copyright © 2023 Lone Dynamics Corporation
